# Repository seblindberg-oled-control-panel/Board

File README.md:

# OLED Control Panel Board

## Revisions

Board revisions are kept as tags in git. The board is generally tagged when the files have been sent off for manufacturing. To export a specific revision, simply run

```
$ git archive --format zip -o /path/to/rev-a.zip 9e7148
```

where the hash of the tag can be found by running `git show rev-a` for the specific tag.

## Scripts

A ruby script is included for generating EAGLE commands that place some of the more repetitive components. There are tools in EAGLE for achieving the same thing and they are most likely better, but a) I did not know that at the time and b) doing it yourself is often more flexible. 

To run the scripts you need to locate the Scripts folder in your terminal of choice and type `ruby place_leds.rb`. Then press `enter` and copy the output into the command input in EAGLE.

## Docs

The documentation is located in another repository and included here as a submodule. To get it after cloning you need to run

```
$ git submodule init
$ git submodule update
```

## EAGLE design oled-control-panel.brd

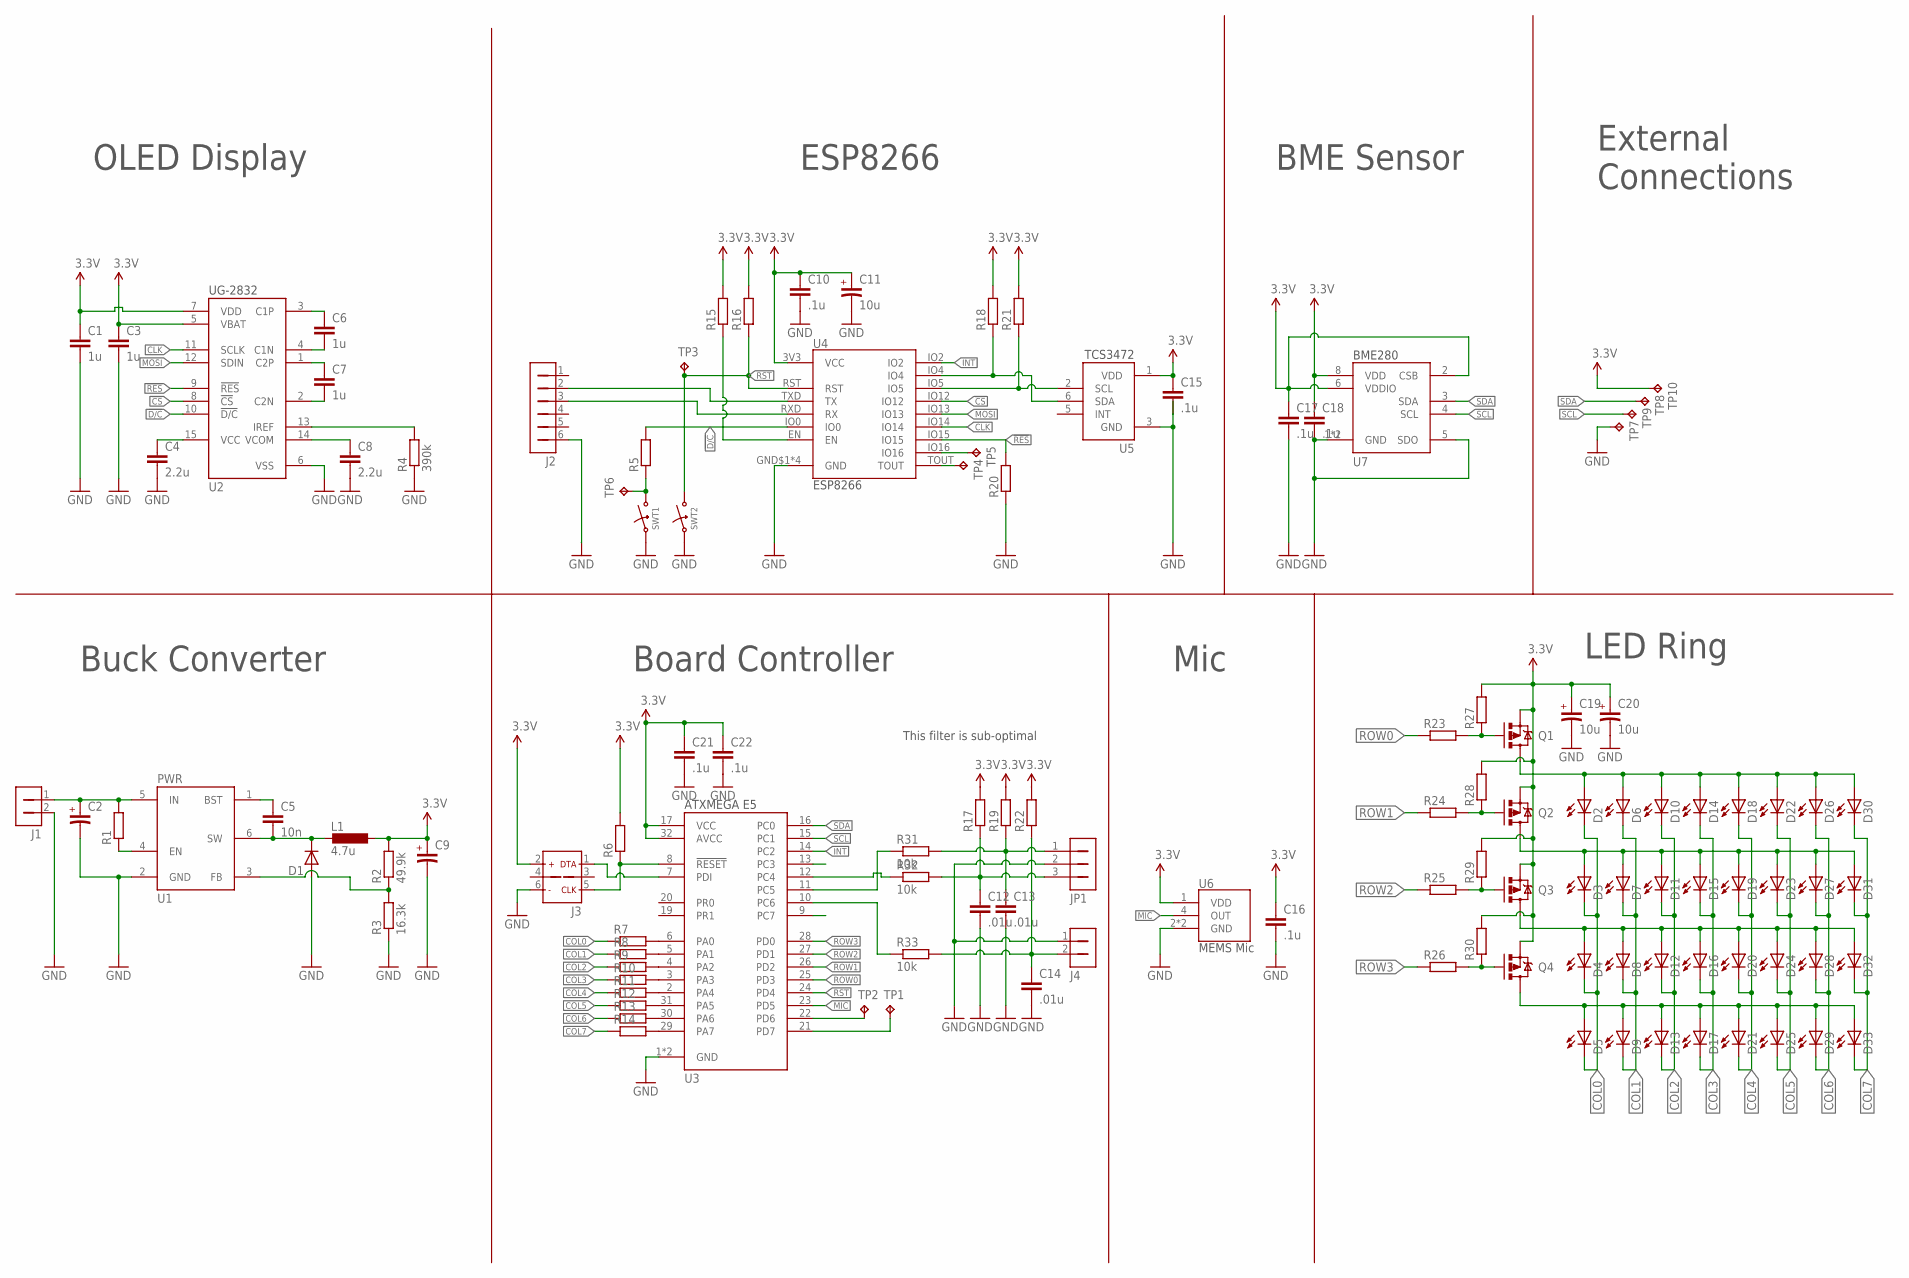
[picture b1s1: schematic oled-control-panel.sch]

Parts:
C1, C3, C6, C7: 1u; 0805
C2, C9: C_POL_1206; 1206_POL
C4, C8: 2.2u; 0805
C5: 10n; 0805
C10, C15, C16, C17, C18, C21, C22: .1u; 0603
C11, C19, C20: 10u; 1206_POL
C12, C13, C14: .01u; 0805
D1: D_FM581X; DO-214AC
D2, D3, D4, D5, D6, D7, D8, D9, D10, D11, D12, D13, D14, D15, D16, D17, D18, D19, D20, D21, D22, D23, D24, D25, D26, D27, D28, D29, D30, D31, D32, D33: LED_0805; 0805_LED
J1, J4: 1X2_MOLEX_53254
J2: 1X6_SMD_RIGHT
J3: PDI_SMD; ISP_SMD
JP1: 1X3_MOLEX_53254
L1: 4.7u; 1210
Q1, Q2, Q3, Q4: PMV160UP; SOT23
R1: R_0805; 0805
R2: 49.9k; 0805
R3: 16.3k; 0805
R4: 390k; 0805
R5, R6, R7, R8, R9, R10, R11, R12, R13, R14, R15, R16, R17, R18, R19, R20, R21, R22, R23, R24, R25, R26, R27, R28, R29, R30: R_0603; 0603
R31, R32, R33: 10k; 0603
SWT1, SWT2: BUTTON_SMD_2P; BTN_SMD_2PIN
TP1, TP2, TP3, TP4, TP5, TP6, TP7, TP8, TP9, TP10: TPTP15R; TP15R
U1: AP3211; SOT23-6
U2: UG-2832HSWEG04
U3: ATXMEGA_E5_TQFP; TQFP32
U4: ESP8266_13; ESP13
U5: TCS3472
U6: SPW2430HR5H_B
U7: BME280

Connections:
3.3V: C1.1, C3.1, C9.1, C10.1, C11.1, C15.1, C16.1, C17.1, C18.1, C19.1, C20.1, C21.1, C22.1, J3.2 (VCC), L1.2, Q1.2 (S), Q2.2 (S), Q3.2 (S), Q4.2 (S), R2.2, R6.2, R15.2, R16.2, R17.2, R18.2, R19.2, R21.2, R22.2, R27.2, R28.2, R29.2, R30.2, TP10.TP, U2.5 (VBAT), U2.7 (VDD), U3.17 (VCC), U3.32 (AVCC), U4.3V3 (VCC), U5.1 (VDD), U6.1 (VDD), U7.2 (CSB), U7.6 (VDDIO), U7.8 (VDD)
!CS: U2.8 (!CS), U4.IO12
!D/C: R5.2, U2.10 (!D/C), U4.IO0
!RES: R20.2, U2.9 (!RES), U4.IO15
A: C12.1, JP1.3, R17.1, R32.2
B: R31.1, U3.11 (PC5)
BTN: C14.1, J4.2, R22.1, R33.2
CLK: U2.11 (SCLK), U4.IO14
COL0: D2.C, D3.C, D4.C, D5.C, R7.1
COL1: D6.C, D7.C, D8.C, D9.C, R8.1
COL2: D10.C, D11.C, D12.C, D13.C, R9.1
COL3: D14.C, D15.C, D16.C, D17.C, R10.1
COL4: D18.C, D19.C, D20.C, D21.C, R11.1
COL5: D22.C, D23.C, D24.C, D25.C, R12.1
COL6: D26.C, D27.C, D28.C, D29.C, R13.1
COL7: D30.C, D31.C, D32.C, D33.C, R14.1
GND: C1.2, C2.2, C3.2, C4.2, C8.2, C9.2, C10.2, C11.2, C12.2, C13.2, C14.2, C15.2, C16.2, C17.2, C18.2, C19.2, C20.2, C21.2, C22.2, D1.A, J1.2, J2.6, J3.6 (GND), J4.1, JP1.2, R3.1, R4.1, R20.1, SWT1.1, SWT2.1, TP7.TP, U1.2 (GND), U2.6 (VSS), U3.1 (GND), U3.18 (GND), U4.GND$1 (GND), U4.GND$2 (GND), U4.GND$3 (GND), U4.GND$4 (GND), U5.3 (GND), U6.2 (GND), U6.3 (GND), U7.1 (GND), U7.5 (SDO), U7.7 (GND)
INT: U3.14 (PC2), U4.IO2
MIC: U3.23 (PD5), U6.4 (OUT)
MOSI: U2.12 (SDIN), U4.IO13
unnamed: C6.1, U2.3 (C1P)
unnamed: C6.2, U2.4 (C1N)
unnamed: C7.1, U2.1 (C2P)
unnamed: C7.2, U2.2 (C2N)
unnamed: R4.2, U2.13 (IREF)
unnamed: C8.1, U2.14 (VCOM)
unnamed: C2.1, J1.1, R1.2, U1.5 (IN)
unnamed: C5.1, U1.1 (BST)
unnamed: C4.1, U2.15 (VCC)
unnamed: C5.2, D1.C, L1.1, U1.6 (SW)
unnamed: R2.1, R3.2, U1.3 (FB)
unnamed: R1.1, U1.4 (EN)
unnamed: J3.5 (CLK), R6.1, U3.8 (!RESET)
unnamed: Q1.1 (G), R23.2, R27.1
unnamed: Q2.1 (G), R24.2, R28.1
unnamed: Q3.1 (G), R25.2, R29.1
unnamed: Q4.1 (G), R26.2, R30.1
unnamed: J3.1 (DATA), U3.7 (PDI)
unnamed: R7.2, U3.6 (PA0)
unnamed: R8.2, U3.5 (PA1)
unnamed: D3.A, D7.A, D11.A, D15.A, D19.A, D23.A, D27.A, D31.A, Q2.3 (D)
unnamed: D4.A, D8.A, D12.A, D16.A, D20.A, D24.A, D28.A, D32.A, Q3.3 (D)
unnamed: D5.A, D9.A, D13.A, D17.A, D21.A, D25.A, D29.A, D33.A, Q4.3 (D)
unnamed: D2.A, D6.A, D10.A, D14.A, D18.A, D22.A, D26.A, D30.A, Q1.3 (D)
unnamed: R9.2, U3.4 (PA2)
unnamed: R10.2, U3.3 (PA3)
unnamed: R11.2, U3.2 (PA4)
unnamed: R12.2, U3.31 (PA5)
unnamed: R13.2, U3.30 (PA6)
unnamed: R14.2, U3.29 (PA7)
unnamed: R5.1, SWT1.2, TP6.TP
unnamed: TP5.TP, U4.IO16
unnamed: J2.2, U4.TXD (TX)
unnamed: J2.3, U4.RXD (RX)
unnamed: R15.1, U4.EN
unnamed: R32.1, U3.12 (PC4)
unnamed: R33.1, U3.10 (PC6)
unnamed: C13.1, JP1.1, R19.1, R31.2
unnamed: TP4.TP, U4.TOUT
unnamed: TP2.TP, U3.22 (PD6)
unnamed: TP1.TP, U3.21 (PD7)
ROW0: R23.1, U3.25 (PD3)
ROW1: R24.1, U3.26 (PD2)
ROW2: R25.1, U3.27 (PD1)
ROW3: R26.1, U3.28 (PD0)
RST: R16.1, SWT2.2, TP3.TP, U3.24 (PD4), U4.RST
SCL: R21.1, TP9.TP, U3.15 (PC1), U4.IO5, U5.2 (SCL), U7.4 (SCL)
SDA: R18.1, TP8.TP, U3.16 (PC0), U4.IO4, U5.6 (SDA), U7.3 (SDA)

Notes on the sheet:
ESP8266
BME Sensor
LED Ring
Board Controller
Buck Converter
OLED Display
Mic
External Connections
This filter is sub-optimal

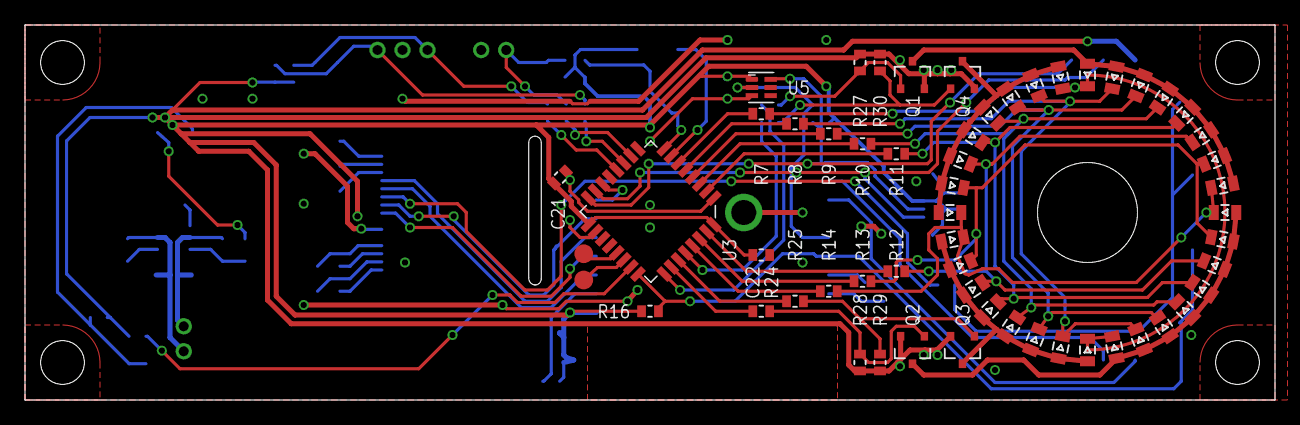
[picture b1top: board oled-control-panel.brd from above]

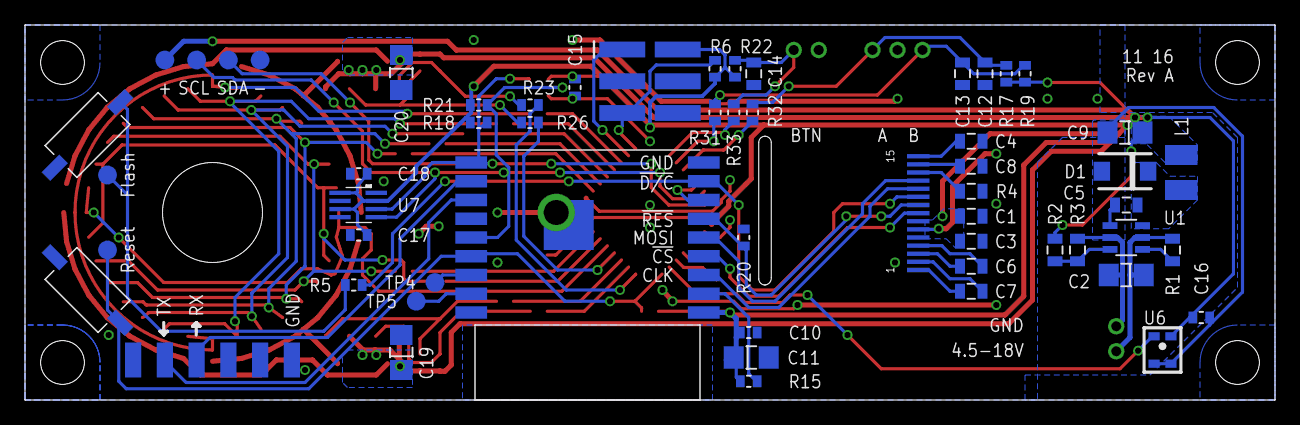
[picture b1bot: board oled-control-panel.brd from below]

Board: 2 copper layers, 100.0 x 30.0 mm, 117 parts (60 on the bottom side), 68 nets.

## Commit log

2018-01-10 Added a readme
2018-01-10 Added the Github wiki as a submodule
2018-01-10 Included the design drawings from the Docs
2018-01-10 Trying different urls for the images
2018-01-10 Trying absolute urls for the assets
2018-01-10 Updated the wiki with a drawing of revision A of the board
2018-01-10 Updated the docs
2018-01-10 Added some notes on how to clone the docs

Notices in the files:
parts and their libraries:
SparkFun-Aesthetics: Licensing: CC v3.0 Share-Alike You are welcome to use this library for commercial purposes.
